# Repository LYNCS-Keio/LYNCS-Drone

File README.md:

# LYNCS-Drone

## Todo
- [ ] ESP32とRaspberry Pi 3間でUARTを使えるようにする
- [x] ESP32でSPI(ESP32がmaster)を使えるようにする
- [ ] MPU9255から姿勢を取得する
- [x] DPS310から温度・気圧を取得する
- [x] DPS310から高度を取得する
- [ ] ESCを使えるようにする
- [ ] 制御する

# Appearance
## 基板完成予想図

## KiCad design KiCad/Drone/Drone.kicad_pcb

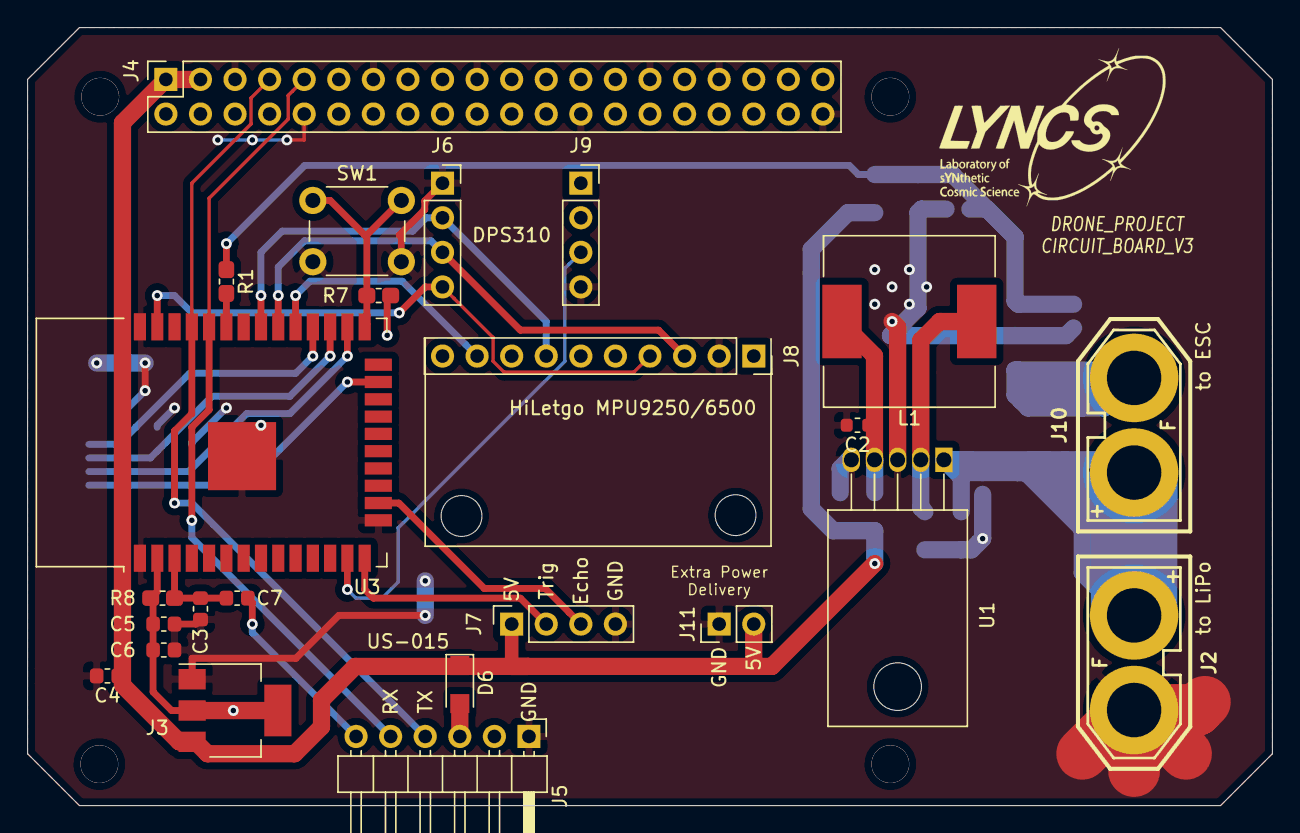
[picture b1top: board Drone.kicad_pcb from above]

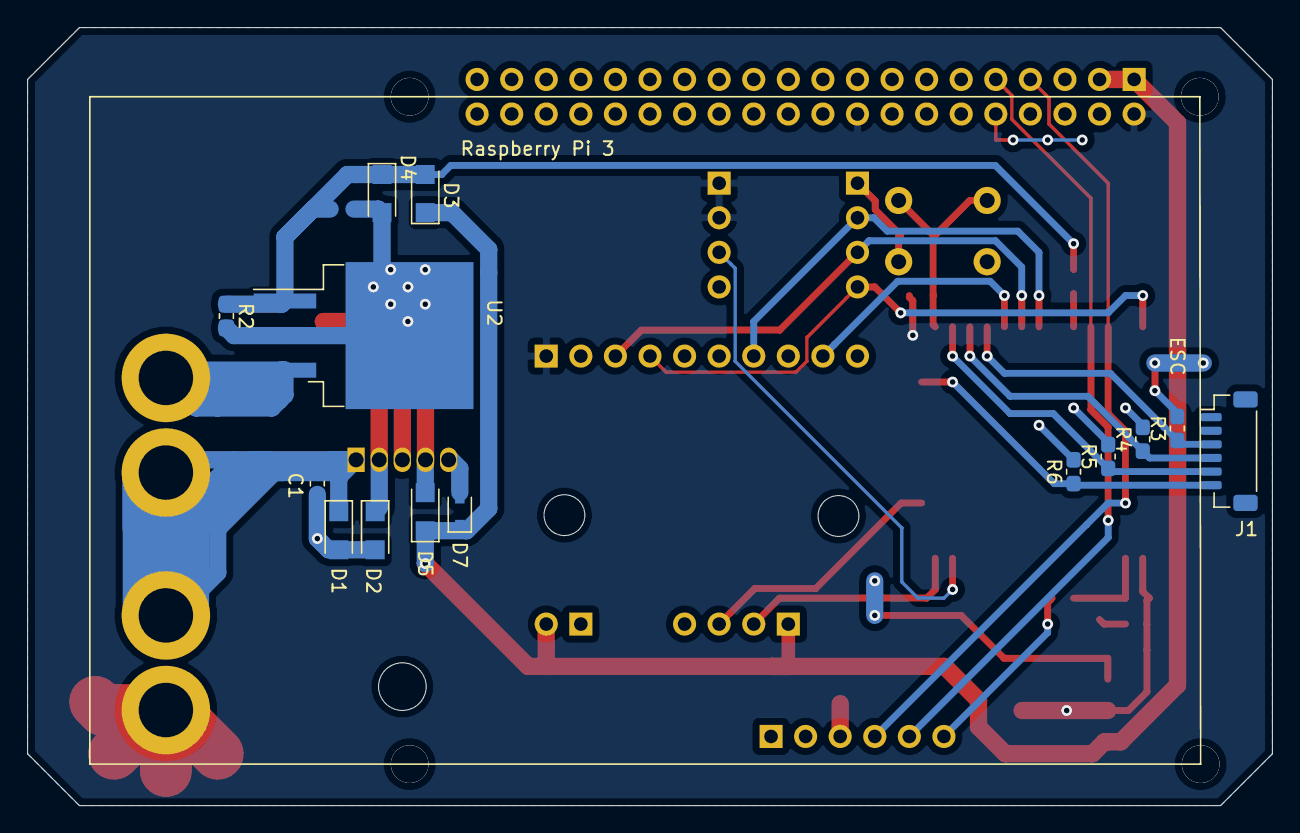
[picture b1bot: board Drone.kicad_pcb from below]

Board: 2 copper layers, 91.4 x 57.1 mm, 40 parts (14 on the bottom side), 26 nets.

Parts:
C1: 47u; C_0603_1608Metric
C2: 22u; C_0603_1608Metric
C3: 1u; C_0603_1608Metric
C4, C5, C7: 0.1uF; C_0603_1608Metric
C6: 22uF; C_0603_1608Metric
D1, D2, D3, D4, D5, D6: SS2040FL; D_SOD-123F
D7: UDZV5.1B; D_SOD-323
J1: ESC; JST_SH_BM06B-SRSS-TB_1x06-1MP_P1.00mm_Vertical
J2: BATTRY; XT-60_female
J3: AZ1086H-3.3; SOT-223-3_TabPin2
J4: Raspberry Pi; PinSocket_2x20_P2.54mm_Vertical
J5: Conn_01x06_Female; PinHeader_1x06_P2.54mm_Horizontal
J6: DPS310_LEFT; PinSocket_1x04_P2.54mm_Vertical
J7: US-015; PinSocket_1x04_P2.54mm_Vertical
J8: MPU9250; PinSocket_1x10_P2.54mm_Vertical
J9: DPS310_RIGHT; PinSocket_1x04_P2.54mm_Vertical
J10: to ESC Power; XT-60_female
J11: Conn_01x02_Female; PinHeader_1x02_P2.54mm_Vertical
L1: 989BS-270M; L_12x12mm_H6mm
R1: 1k; R_0603_1608Metric_Pad1.05x0.95mm_HandSolder
R2, R3, R4, R5, R6, R7, R8: 10k; R_0603_1608Metric_Pad1.05x0.95mm_HandSolder
SW1: SW_Push; SW_PUSH_6mm
U1: LM2596T-5; TO-220-5_Horizontal_TabDown
U2: SKI03021; TO-263-3_TabPin4
U3: ESP32-WROOM-32
screw: MountingHole_3mm
screw#2: MountingHole_3mm

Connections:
3V3: C5.1, C6.1, J3.2, J4.2, J4.18, J8.1, J9.1, J9.2, R7.1, R8.2, U3.2
5V: C4.1, D3.1, D5.1, D6.1, D7.1, J3.3, J4.1, J4.3, J7.1, J11.2
ADO: J6.2, J8.7, U3.31
BAT: C1.1, D1.1, J2.2, J10.2, U1.1
CSBN: J9.3, U3.13
ESC_GND: J10.1, U2.3
ESP_EN: C3.2, C7.1, R8.1, U3.3
ESP_RX: J4.9, J5.5, U3.34
ESP_TX: J4.7, J5.4, U3.35
Echo: J7.3, U3.16
GND: C1.2, C2.2, C3.1, C4.2, C5.2, C6.2, D1.2, D2.2, D4.2, D7.2, J2.1, J3.1, J4.5, J4.10, J4.13, J4.19, J4.26, J4.29, J4.33, J4.40, J5.1, J6.1, J7.4, J8.2, J9.4, J11.1, R2.2, R3.2, R4.2, R5.2, R6.2, SW1.2, U1.3, U1.5, U2.2, U2.4, U3.1, U3.15, U3.38, U3.39
GPIO4: J1.5, R5.1, U3.26
GPIO5: J8.9, U3.29
GPIO12: J7.2, U3.14
GPIO15: J1.6, R6.1, U3.23
GPIO16: J1.4, R4.1, U3.27
GPIO17: J1.3, R3.1, U3.28
GPIO18: J6.3, J8.3, U3.30
GPIO21: R1.2, U3.33
GPIO23: J6.4, J8.4, U3.37
unnamed: C2.1, D5.2, L1.2, U1.4
unnamed: C7.2, J5.6
unnamed: D2.1, L1.1, U1.2
unnamed: D3.2, D4.1, R1.1, R2.1, U2.1
unnamed: D6.2, J5.3
unnamed: R7.2, SW1.1, U3.25

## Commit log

2019-07-11 [ADD].gitignore
2019-07-22 platform ioを用いたCI開発環境
2019-07-22 .travis.ymlはrootになければならない
2019-07-22 Platform IO (#4)
    * platform ioを用いたCI開発環境
    * .travis.ymlはrootになければならない
2019-07-23 libraryの削除
2019-07-23 renamed main.cpp
2019-07-23 C++用に変更
2019-07-23 I2Cbusを使おう
2019-07-23 I2C libs (#5)
    * Initial commit, beta state
    * Reestrutured directory and added example/test
    * adjusted log level to verbose to debug lib
    * redone directory structure
    * Created menu options for I2Cbus in menuconfig
    * add initial readme.md
2019-07-24 PID制御クラスの追加
2019-07-24 積分してなかった
2019-07-24 [ADD]PID lib (#7)
    * PID制御クラスの追加
    * 積分してなかった
2019-08-07 dps310のlib（温度検出まで）
2019-08-15 [ADD]dps_err_t
2019-08-15 [ADD]flushFIFO(
2019-08-15 [ADD] Mode
2019-08-16 [ADD]writeByteBitfield
2019-08-16 [UP]writeByteBitfield
2019-08-16 [ADD]resisters
2019-08-16 [UP]fifoflush
2019-08-16 [ADD]readByteBitField
2019-08-16 [UP]initiarize
2019-08-16 [ADD]readcoef
2019-08-16 [ADD]setOpMode
2019-08-16 [ADD]disableFIFO
2019-08-16 [ADD]standby
2019-08-16 [ADD]configTemp
2019-08-16 [ADD]config
2019-08-16 [ADD]startMeasureTempOnce
2019-08-16 [ADD]some functions
2019-08-16 [ADD]measureTempOnce
2019-08-16 [ADD]startMeasurePressureOnce
2019-09-12 [ADD] MPU class
2019-09-12 [ADD]measurePressureOnce
2019-09-12 [ADD]KiCad_Schematics
2019-09-13 SPIでMPU9250のデータを取る,SPIbusはまだ使っていません
2019-09-13 [DEL]deleted measure_control_
2019-09-13 [DEL]deleted tmp_rate_
2019-09-13 [DEL]deleted tmp_ext_flag_
2019-09-13 [add]lib/MPU9250
2019-09-13 [add]lib\UART
2019-09-16 [MOD]CS_PINの変更
2019-09-16 [MOD]CS_PINの変更（回路の変更を含む）
2019-09-16 [MOD]sampling interval must be over 10ms
2019-09-16 [DEL]deleted the function temperature
2019-09-16 [DEL]deleted tmp_scale_factor
2019-09-16 [ADD]measureHeightOnce
2019-09-16 [FIX]設定と書き込み関数の修正
2019-09-17 [MOD]測定間隔の単位の修正
2019-09-17 [MOD]補正値が間違っていた
2019-09-17 [MOD]高度の計算式の修正
2019-09-17 [ADD]prs_over_sampling_rate
2019-09-17 [MOD]改行の修正
2019-09-17 [MOD]initializeの修正
2019-09-17 [ADD] configTemp & configPressure
2019-09-17 [ADD]DPS310__OSR_SE
2019-09-17 [FIX]flushFIFO ここがすべての元凶である！！！！！！！！！スペルはちゃんと確認しようね
2019-09-17 [MOD]仮想関数の明示
2019-09-17 [MOD]modified initialize()
2019-09-17 [MOD]m_initFailは正常初期化時に0になる
2019-09-17 [FIX?]よくわからんけど動く(?)プログラムです なんだこれ(print入れたりdelay追加すると死ぬ)
2019-09-17 [DEL]measureHeightOnceの廃止
2019-09-17 [FIX?]よくわからんけど動く(?)プログラムです なんだこれ(print入れたりdelay追加すると死ぬ)
    SPIの通信周りは自分で作らない方が良いのか…？
2019-09-18 [MOD]pigpio用のファイルを移動しました
2019-09-18 [FIX]configの書き込み順を変えて少し安定した気がする レジスタに正しい値が書き込まれるようになった
2019-09-18 [FIX]spiWriteの中にdelayを置くと書き込みに失敗しなくなった 一方で電源を一回落とさないで連続で書き込むと読み取りに失敗してしまう
2019-09-18 [ADD]LICENCE
2019-09-18 [DEL]deleted calc_height_sub
2019-09-18 [ADD]DPS__FAIL_COMMUNICATION
2019-09-18 [MOD]定数の移動
2019-09-18 [MOD]DPS310__BUSYTIME_FAILSAFE
2019-09-18 mcpwm使うとうまく行った
2019-09-18 remove unnecessary comment
2019-09-19 [MOD]外部5V電源とマイナーな変更
2019-09-19 [MOD]minor change
2019-09-19 [MOD]minor change (#15)
2019-09-19 [MOD]UARTピンの変更
2019-09-19 add pipfile
2019-09-19 [MOD]esp_err_tを使わないようにした
2019-09-19 bit bang uart test
2019-09-19 [MOD]esp_err_tの削除 (#17)
    * [ADD]LICENCE
    * [DEL]deleted calc_height_sub
    * [ADD]DPS__FAIL_COMMUNICATION
    * [MOD]定数の移動
    * [MOD]DPS310__BUSYTIME_FAILSAFE
    * [MOD]esp_err_tを使わないようにした
2019-09-19 modify
2019-09-19 format receiving data
2019-09-19 [ADD]commit template
2019-09-19 [MOD]シルクスクリーンのマイナーな変更 (#16)
    * [MOD]minor change
    * [MOD]minor change
    * [MOD]UARTピンの変更
2019-09-19 [ADD]US015とMPUDriver
2019-09-19 [ADD]US015
2019-09-19 modify pipfile
2019-09-19 [FIX]ArduinoIDE用プログラム
    回路確認用に作りました
2019-09-19 [ADD]commit template (#18)
2019-09-19 [FIX]:recycle: fixed typo
2019-09-19 [FIX]:recycle: fixed typo (#19)
2019-09-19 [MOD]:bug:MOSFET周りの修正
2019-09-20 :pencil2: wrote some discriptions
2019-09-20 :recycle:#defineをconstexprに変えた
2019-09-20 [ADD]#3
2019-09-20 :recycle:銅線を太くしたり
2019-09-20 [MOD]:recycle:回路の変更 (#21)
    * [MOD]minor change
    * [MOD]minor change
    * [MOD]UARTピンの変更
    * [MOD]:bug:MOSFET周りの修正
    * :recycle:銅線を太くしたり
2019-09-21 :recycle:deleted unused #include
2019-09-21 :recycle:cleaned DPSdriver (#22)
    * [ADD]LICENCE
    * [DEL]deleted calc_height_sub
    * [ADD]DPS__FAIL_COMMUNICATION
    * [MOD]定数の移動
    * [MOD]DPS310__BUSYTIME_FAILSAFE
    * [MOD]esp_err_tを使わないようにした
2019-09-21 :bug:ESCの位置と回路の変更
2019-09-21 :recycle:updated MPUdriver
2019-09-21 とりあえずパケット生成
2019-09-22 :recycle:微調整
2019-09-22 :+1:added MPU9255 class
2019-09-22 :recycle:deleted unused constants
2019-09-23 :recycle:ESCの位置を変更
2019-09-24 create pdu
2019-09-25 :thinking_face:added measureHeightOnce
2019-09-25 :bug:回路の変更 (#23)
    * :bug:ESCの位置と回路の変更
    * :recycle:微調整
    * :recycle:ESCの位置を変更
2019-09-25 :+1:add measureHeightOnce (#24)
    * :recycle:deleted unused constants
    * :thinking_face:added measureHeightOnce
2019-09-25 :recycle:renamed DPS__FAIL_TOO_BUSY
2019-09-25 :shower:不要なローカル変数の削除
2019-09-25 :bug:standbyを追加
2019-09-25 :shower:deleted unnecessary return
2019-09-25 :shower:fixes #25
2019-09-25 :recycle:regular updates (#26)
    * :shower:不要なローカル変数の削除
    * :recycle:renamed DPS__FAIL_TOO_BUSY
    * :bug:standbyを追加
    * :shower:deleted unnecessary return
    * :shower:fixes #25
2019-09-25 :pencil2:fixed typo
2019-09-25 :shower:removed unused argument
2019-09-25 :truck:ディレクトリの変更
2019-09-26 :recycle:2回以上のdev_initに対応
2019-09-26 :recycle:renamed some variables
2019-09-27 :recycle:refactor DPSdriver (#27)
    * :shower:removed unused argument
    * :recycle:2回以上のdev_initに対応
    * :recycle:renamed some variables
2019-09-27 :fire:dps_init
2019-09-27 :fire:Daily Update DPSdriver (#28)
    * :shower:removed unused argument
    * :recycle:2回以上のdev_initに対応
    * :recycle:renamed some variables
    * :fire:dps_init
2019-09-27 :truck:renamed some variables
2019-09-27 :+1:defined MPU PINS
2019-09-27 :+1:add some register map
2019-09-27 :recycle:コンストラクタの引数を変えた
2019-09-27 :construction:後処理の追加
2019-09-27 :construction:m_dev_init_を追加して2回以上のdev_initに対応した
2019-09-27 :construction:MPUのSPI設定の追加
2019-09-28 :construction:namespace esc
2019-10-02 move roopcounter into static valuable
2019-10-02 :construction:Who Am Iの取得に成功
2019-10-02 mcpwm使うとうまく行った (#13)
    * mcpwm使うとうまく行った
    * remove unnecessary comment
    * :pencil2:fixed typo
    * :construction:namespace esc
    * move roopcounter into static valuable
2019-10-02 :+1:added initialize() to MPU9255 class
2019-10-02 :construction:initializeは間違ったデバイスを検知する
2019-10-02 :+1:added setGyroFullScaleSelect
2019-10-05 :fire:DPS310のソケットの位置を修正
2019-10-05 :construction:setGyroFullScaleSelectを公開
2019-10-05 :sparkles:add measureGyro
2019-10-05 :bug:fixed measureGyro
2019-10-05 :sparkles:add measureAccel
2019-10-05 :+1:add setAccelFullScaleSelect
2019-10-06 :pencil2:シルクの位置を調整
2019-10-06 :fire:テスト用ファイルの削除
2019-10-09 z軸テスト
2019-10-09 modify EXT_SYNC_SET
2019-10-25 :+1:added MPU9250driver
2019-11-01 :bug:raspberry pi の配置の修正など
2019-11-08 :+1:update schematic
2019-11-16 :+1:mosfetの保護
2019-12-03 :+1:update schematic ver3
2019-12-03 :+1:gerber data
2020-01-07 :+1:fixed footprint
2020-02-07 [add]Rotor
